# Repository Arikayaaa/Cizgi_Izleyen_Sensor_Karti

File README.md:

# Cizgi_Izleyen_Sensor_Karti
## Hem analog hem digital cikis verebilen cizgi izleyen sensor

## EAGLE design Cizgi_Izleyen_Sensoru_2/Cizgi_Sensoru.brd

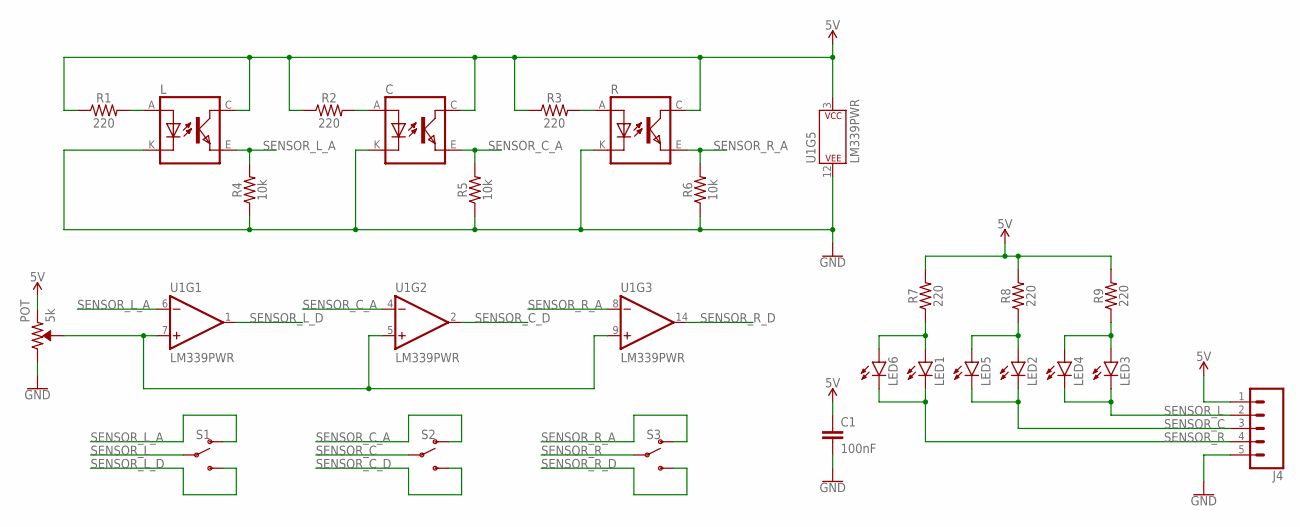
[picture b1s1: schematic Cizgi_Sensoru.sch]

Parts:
C: TCRT5000
C1: 100nF; 0805
J4: CONN_05; 1X05
L: TCRT5000
LED1, LED2, LED3, LED4, LED5, LED6: LEDSML0805; SML0805
POT: 5k; TRIMPOT-SMD-5MM
R: TCRT5000
R1, R2, R3, R7, R8, R9: 220; 0805
R4, R5, R6: 10k; 0805
S1, S2, S3: SWITCH-SPDT-SMD-RIGHT-ANGLE; SWITCH_SPST_SMD_A
U1: LM339PWR; TSSOP-14

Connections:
5V: C.C (COLLECTOR), C1.1, J4.1, L.C (COLLECTOR), POT.A (CCW), R.C (COLLECTOR), R1.1, R2.1, R3.1, R7.2, R8.2, R9.2, U1.3 (P$V+)
GND: C.K (CATHODE), C1.2, J4.5, L.K (CATHODE), POT.C (CW), R.K (CATHODE), R4.1, R5.1, R6.1, U1.12 (P$V-)
unnamed: L.A (ANODE), R1.2
unnamed: C.A (ANODE), R2.2
unnamed: R.A (ANODE), R3.2
unnamed: POT.B (WIPER), U1.5 (+IN), U1.7 (+IN), U1.9 (+IN)
unnamed: LED1.A, LED6.A, R7.1
unnamed: LED2.A, LED5.A, R8.1
unnamed: LED3.A, LED4.A, R9.1
SENSOR_C: J4.3, LED2.C, LED5.C, S2.2
SENSOR_C_A: C.E (EMITTER), R5.2, S2.1 (O), U1.4 (-IN)
SENSOR_C_D: S2.3 (S), U1.2 (OUT)
SENSOR_L: J4.2, LED3.C, LED4.C, S1.2
SENSOR_L_A: L.E (EMITTER), R4.2, S1.1 (O), U1.6 (-IN)
SENSOR_L_D: S1.3 (S), U1.1 (OUT)
SENSOR_R: J4.4, LED1.C, LED6.C, S3.2
SENSOR_R_A: R.E (EMITTER), R6.2, S3.1 (O), U1.8 (-IN)
SENSOR_R_D: S3.3 (S), U1.14 (OUT)

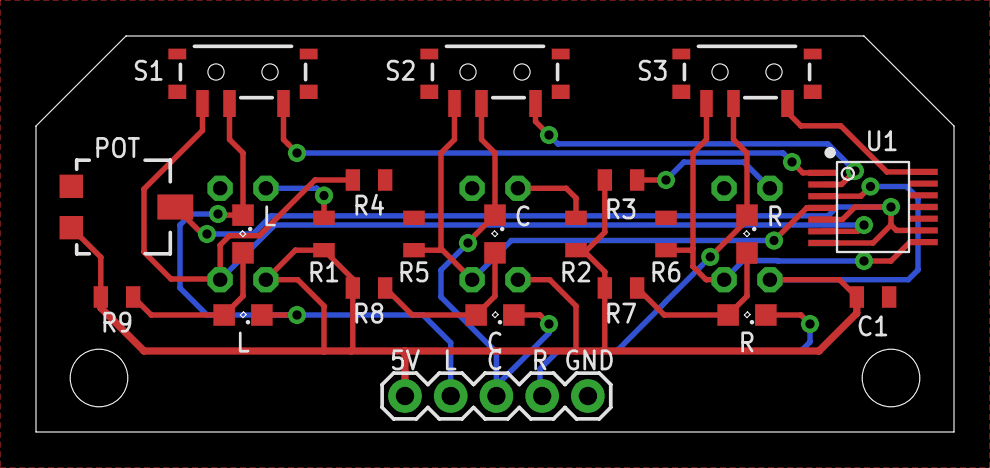
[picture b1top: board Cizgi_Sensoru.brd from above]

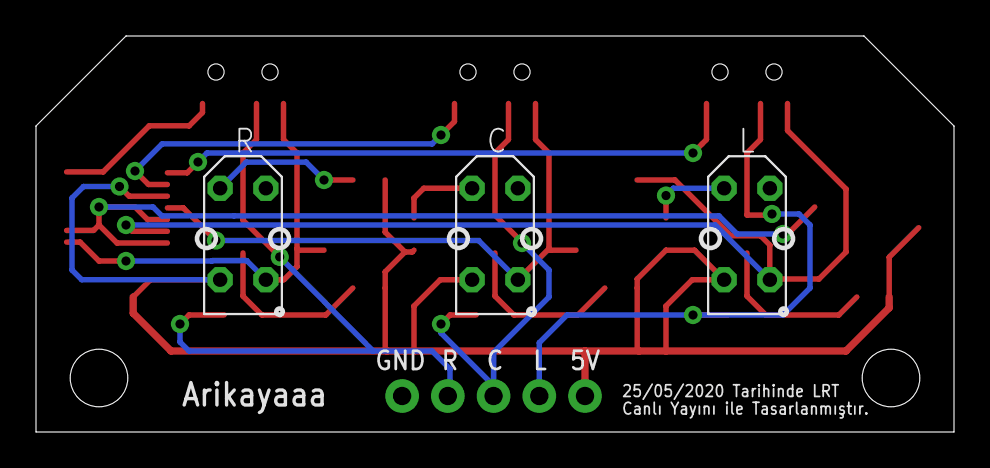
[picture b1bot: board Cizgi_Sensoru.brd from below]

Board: 2 copper layers, 51.0 x 22.0 mm, 25 parts (3 on the bottom side), 18 nets.

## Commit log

2020-05-25 v1.00
2022-05-19 v1.01
    Unnecessary recovery files were deleted.
2022-05-20 v1.01
    Codes and PCB were added

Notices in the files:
parts and their libraries:
SparkFun-Capacitors: Licensing: Creative Commons ShareAlike 4.0 International - https://creativecommons.org/licenses/by-sa/4.0
